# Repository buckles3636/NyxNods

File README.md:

# NyxNods
Open Source Analog Night Vision Housing &amp; Controller

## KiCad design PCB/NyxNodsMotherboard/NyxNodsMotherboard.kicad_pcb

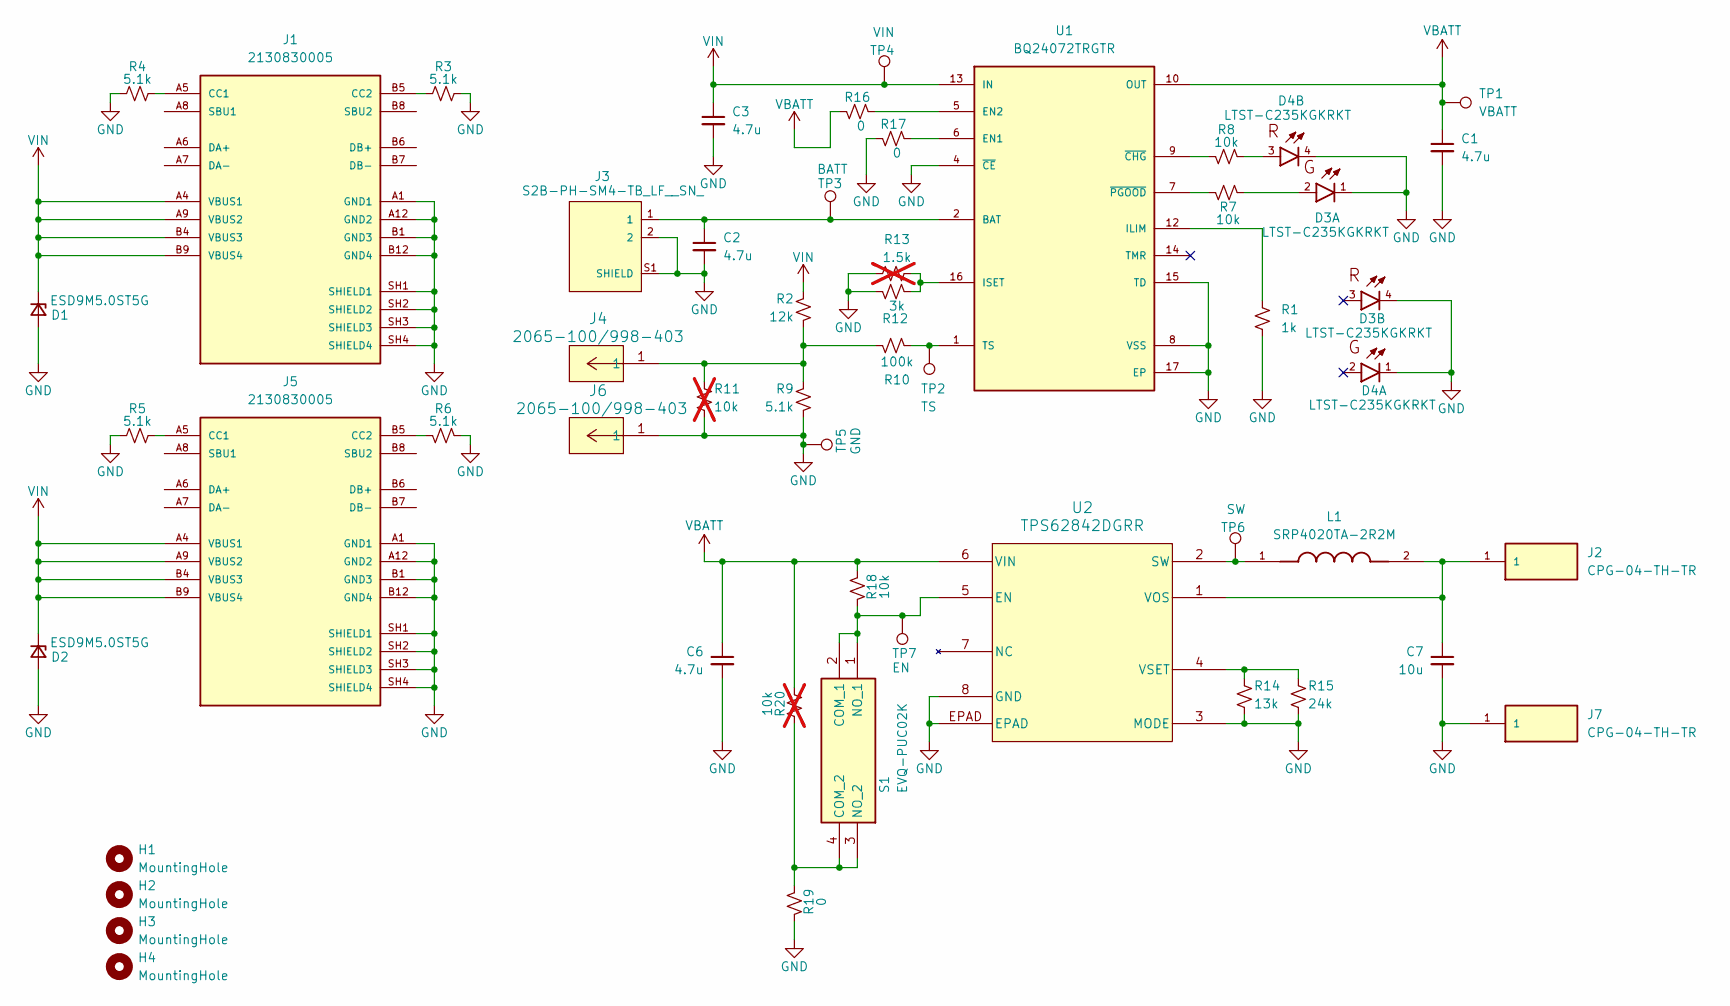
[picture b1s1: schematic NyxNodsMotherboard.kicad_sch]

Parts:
C1, C2, C3, C6: 4.7u; C_0402_1005Metric
C7: 10u; C_0402_1005Metric
D1, D2: ESD9M5.0ST5G; D_SOD-923
D3, D4: LTST-C235KGKRKT; LED_LTST-C235KGKRKT
H1, H2, H3, H4: MountingHole; MountingHole_1.8mm_M1.6_ISO14580_Pad_TopBottom
J1, J5: 2130830005; MOLEX_2130830005; PARTREV A1
J2, J7: CPG-04-TH-TR; SAMESKY_CPG-04-TH-TR; PARTREV 1.01
J3: S2B-PH-SM4-TB_LF__SN_; JST_S2B-PH-SM4-TB_LF__SN_
J4, J6: 2065-100/998-403; CONN_2065-100&slash_998-403_WAG
L1: SRP4020TA-2R2M; IND_SRP4020TA-2R2M
R1: 1k; R_0402_1005Metric
R2: 12k; R_0402_1005Metric
R3, R4, R5, R6, R9: 5.1k; R_0402_1005Metric
R7, R8, R18: 10k; R_0402_1005Metric
R10: 100k; R_0402_1005Metric
R11, R20: 10k; R_0402_1005Metric; not fitted
R12: 3k; R_0402_1005Metric
R13: 1.5k; R_0402_1005Metric; not fitted
R14: 13k; R_0402_1005Metric
R15: 24k; R_0402_1005Metric
R16, R17, R19: 0; R_0402_1005Metric
S1: EVQ-PUC02K; EVQPUC02K; Mouser Part Number 667-EVQ-PUC02K
TP1: VBATT; TestPoint_Pad_D1.0mm
TP2: TS; TestPoint_Pad_D1.0mm
TP3: BATT; TestPoint_Pad_D1.0mm
TP4: VIN; TestPoint_Pad_D1.0mm
TP5: GND; TestPoint_Pad_D1.0mm
TP6: SW; TestPoint_Pad_D1.0mm
TP7: EN; TestPoint_Pad_D1.0mm
U1: BQ24072TRGTR; QFN50P300X300X100-17N
U2: TPS62842DGRR; VSSOP_42DGRR_TEX

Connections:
GND: C1.2, C2.2, C3.2, C6.2, C7.2, D1.2 (A), D2.2 (A), D3.1, D3.4, D4.1, D4.4, J1.A1 (GND1), J1.A12 (GND2), J1.B1 (GND3), J1.B12 (GND4), J1.SH1 (SHIELD1), J1.SH2 (SHIELD2), J1.SH3 (SHIELD3), J1.SH4 (SHIELD4), J3.2, J3.S1 (SHIELD), J3.S2 (SHIELD), J5.A1 (GND1), J5.A12 (GND2), J5.B1 (GND3), J5.B12 (GND4), J5.SH1 (SHIELD1), J5.SH2 (SHIELD2), J5.SH3 (SHIELD3), J5.SH4 (SHIELD4), J6.1 (1_1), J7.1 (1_1), R1.2, R3.2, R4.1, R5.1, R6.1, R9.2, R11.2, R12.1, R13.1, R14.2, R15.2, R17.1, R19.2, TP5.1 (1_1), U1.4 (~CE), U1.8 (VSS), U1.15 (TD), U1.17 (EP), U2.3 (MODE), U2.8 (GND), U2.EPAD
unnamed: C2.1, J3.1, TP3.1 (1_1), U1.2 (BAT), U1.3 (BAT)
unnamed: D3.2, R7.1
unnamed: D4.3, R8.1
unnamed: J1.A5 (CC1), R4.2
unnamed: J1.B5 (CC2), R3.1
unnamed: J4.1 (1_1), R2.2, R9.1, R10.1, R11.1
unnamed: J5.A5 (CC1), R5.2
unnamed: J5.B5 (CC2), R6.2
unnamed: R18.2, S1.1 (NO_1), S1.2 (COM_1), TP7.1 (1_1), U2.5 (EN)
unnamed: R19.1, R20.2, S1.3 (NO_2), S1.4 (COM_2)
unnamed: R17.2, U1.6 (EN1)
unnamed: R16.2, U1.5 (EN2)
unnamed: R1.1, U1.12 (ILIM)
unnamed: R12.2, R13.2, U1.16 (ISET)
unnamed: R10.2, TP2.1 (1_1), U1.1 (TS)
unnamed: R8.2, U1.9 (~CHG)
unnamed: R7.2, U1.7 (~PGOOD)
unnamed: L1.1, TP6.1 (1_1), U2.2 (SW)
unnamed: C7.1, J2.1 (1_1), L1.2, U2.1 (VOS)
unnamed: R14.1, R15.1, U2.4 (VSET)
VBATT: C1.1, C6.1, R16.1, R18.1, R20.1, TP1.1 (1_1), U1.10 (OUT), U1.11 (OUT), U2.6 (VIN)
VIN: C3.1, D1.1 (K), D2.1 (K), J1.A4 (VBUS1), J1.A9 (VBUS2), J1.B4 (VBUS3), J1.B9 (VBUS4), J5.A4 (VBUS1), J5.A9 (VBUS2), J5.B4 (VBUS3), J5.B9 (VBUS4), R2.1, TP4.1 (1_1), U1.13 (IN)

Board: 4 copper layers, 51 parts (0 on the bottom side), 23 nets, no tracks yet.

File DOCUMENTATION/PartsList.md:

Pogo Pins: US CPG-04-TH-TR JLC YZD0027-20060-02
Battery Charge / Hotswap IC: bq24072
Buck: TPS62842DGRR
USB: Molex 21308300056
//IMU: LIS2DH12
//USB to SPI: MCP2210T-I/MQ
Inductor: SRP4020TA-2R2M
Power TVS Diode: ESD9M5.0ST5G
//USB TVS Diode: USBLC6-2SC6
Reverse Mount Led:LTST-C235KGKRKT

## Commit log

2026-03-29 File Structure
2026-03-30 Started adding symbols
2026-04-03 updated usb part number
2026-04-12 Airlpane Changes
2026-04-13 Finished battery managment layout
2026-04-13 Changed my mind to use all analog
2026-04-25 Battery Schematic
2026-04-27 Finished Schematic
2026-04-27 Updated with button
2026-04-27 Started Layout
2026-04-27 Layout Progress, 3D models imported
